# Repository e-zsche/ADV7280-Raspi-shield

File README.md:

# ADV7280 based analog video digitizer shield for raspberry pi

Raspberry pi shiel built around the ADV7280 analog video decoder IC. Connection to raspberry pi over
MIPI CSI-2 interface. FFC/FPC connector on the shield has the same pinout as the pi camera connector.

One huge advantage the ADV7280 has over similiar analog video decoders is that the drivers are already
present in the standard raspberry pi linux kernel. All you have to do is enable the driver in the
config.txt file. This shield is more or less plug'n'play.

# Hardware

The whole circuit design is copied exactly from the <a href="https://www.analog.com/media/en/technical-documentation/data-sheets/ADV7280.PDF">ADV7280 datasheet</a>

Video inputs are done with BNC connectors. The only reason is that I got these really cheap so I use
them everywhere. All video inputs are terminated with 75R resistors close to the connector. For
protection there are BAT54S diodes installed on all used inputs. Because of space constraints only
inputs 1 - 4 are available on the PCB.

In the beginning I was unsure how to set the RST, PWRDWN pins of the ADV7280 and how important
the power cycling is when booting the IC. That is what the jumper pins near the raspberry pi's
USB connectors are for. Turns out you can leave them all connected to +3.3V all the time.

I was unsure about the CAM_IO1 and CAM_IO2 pins of the raspberry CSI connector as well. The pins
on the pin header can be left unconnected.

The only really critical traces in my opinion are from the CSI output from the IC to the FFC/FPC
camera connector. Looking at the technical specs in the MIPI CSI standard these traces the traces
should have 100R differential impedance (+/- 10%). To get the correct trace width and spacing I
used kicad's builtin calculation tool and the PCB dimensions of the manufacturer. With these I
fiddled around with the calculation until it was close enough.

This design is routed for ordering at JLCPCB (not sponsored!). This is important because different
manufacturers may have different PCB dimensions, which in turn affects the trace impedance of the
CSI traces. Make sure to get this correct, otherwise the CSI connection may not work reliably.

Until now the shield is running fine and I encountered no problems while running.

# Software

All connections this shield needs for running is the CSI connector to the raspberry pi's camera
interface. Enabling the kernel module for this shield is done in the config.txt file:

```
[all]
# enable adv7280
dtoverlay=adv728x-m,adv7280m=1
```

Done! After booting you should get a ne video device.
You can check this with v4l2-ctl command line utility.

```
$ v4l2-ctl --list-devices
$ v4l2-ctl -D -d 0
```

## setting video standard

Video standard is set to NTSC as default. Change it with this command
```
$ v4l2-ctl --set-standard pal
$ v4l2-ctl --set-standard ntsc
```

## changing inputs

Selecting video input source is not straight forward. This is not streamlined in the driver.
Doing this is a little bit hacky, but it works.

```
$ sudo bash -c "echo 0 > /sys/module/adv7180/parameters/dbg_input"
```

Change the number to the input you want to select. 0 corresponds to input 1 and so forth.
You can check the detected input format with

```
$ v4l2-ctl -S
```

## picture adjustment

Here is the interesting part. You can adjust brightness, saturation and so on inside the ADV7280.
No need to fiddle around with i2c registers. When the driver is loaded the corresponding i2c bus
is not exposed for reading or writing. Instead everything is handled through the v4l2-ctl utility.

To list the available settings use one of these commands:

```
$ v4l2-ctl -d <device> -l
$ v4l2-ctl -d <device> -L
```

This gives a description of all available settings and also shows the value range for each setting. If you want to change something use this command:

```
$ v4l2-ctl -d <device> -c <setting>=<value>
```

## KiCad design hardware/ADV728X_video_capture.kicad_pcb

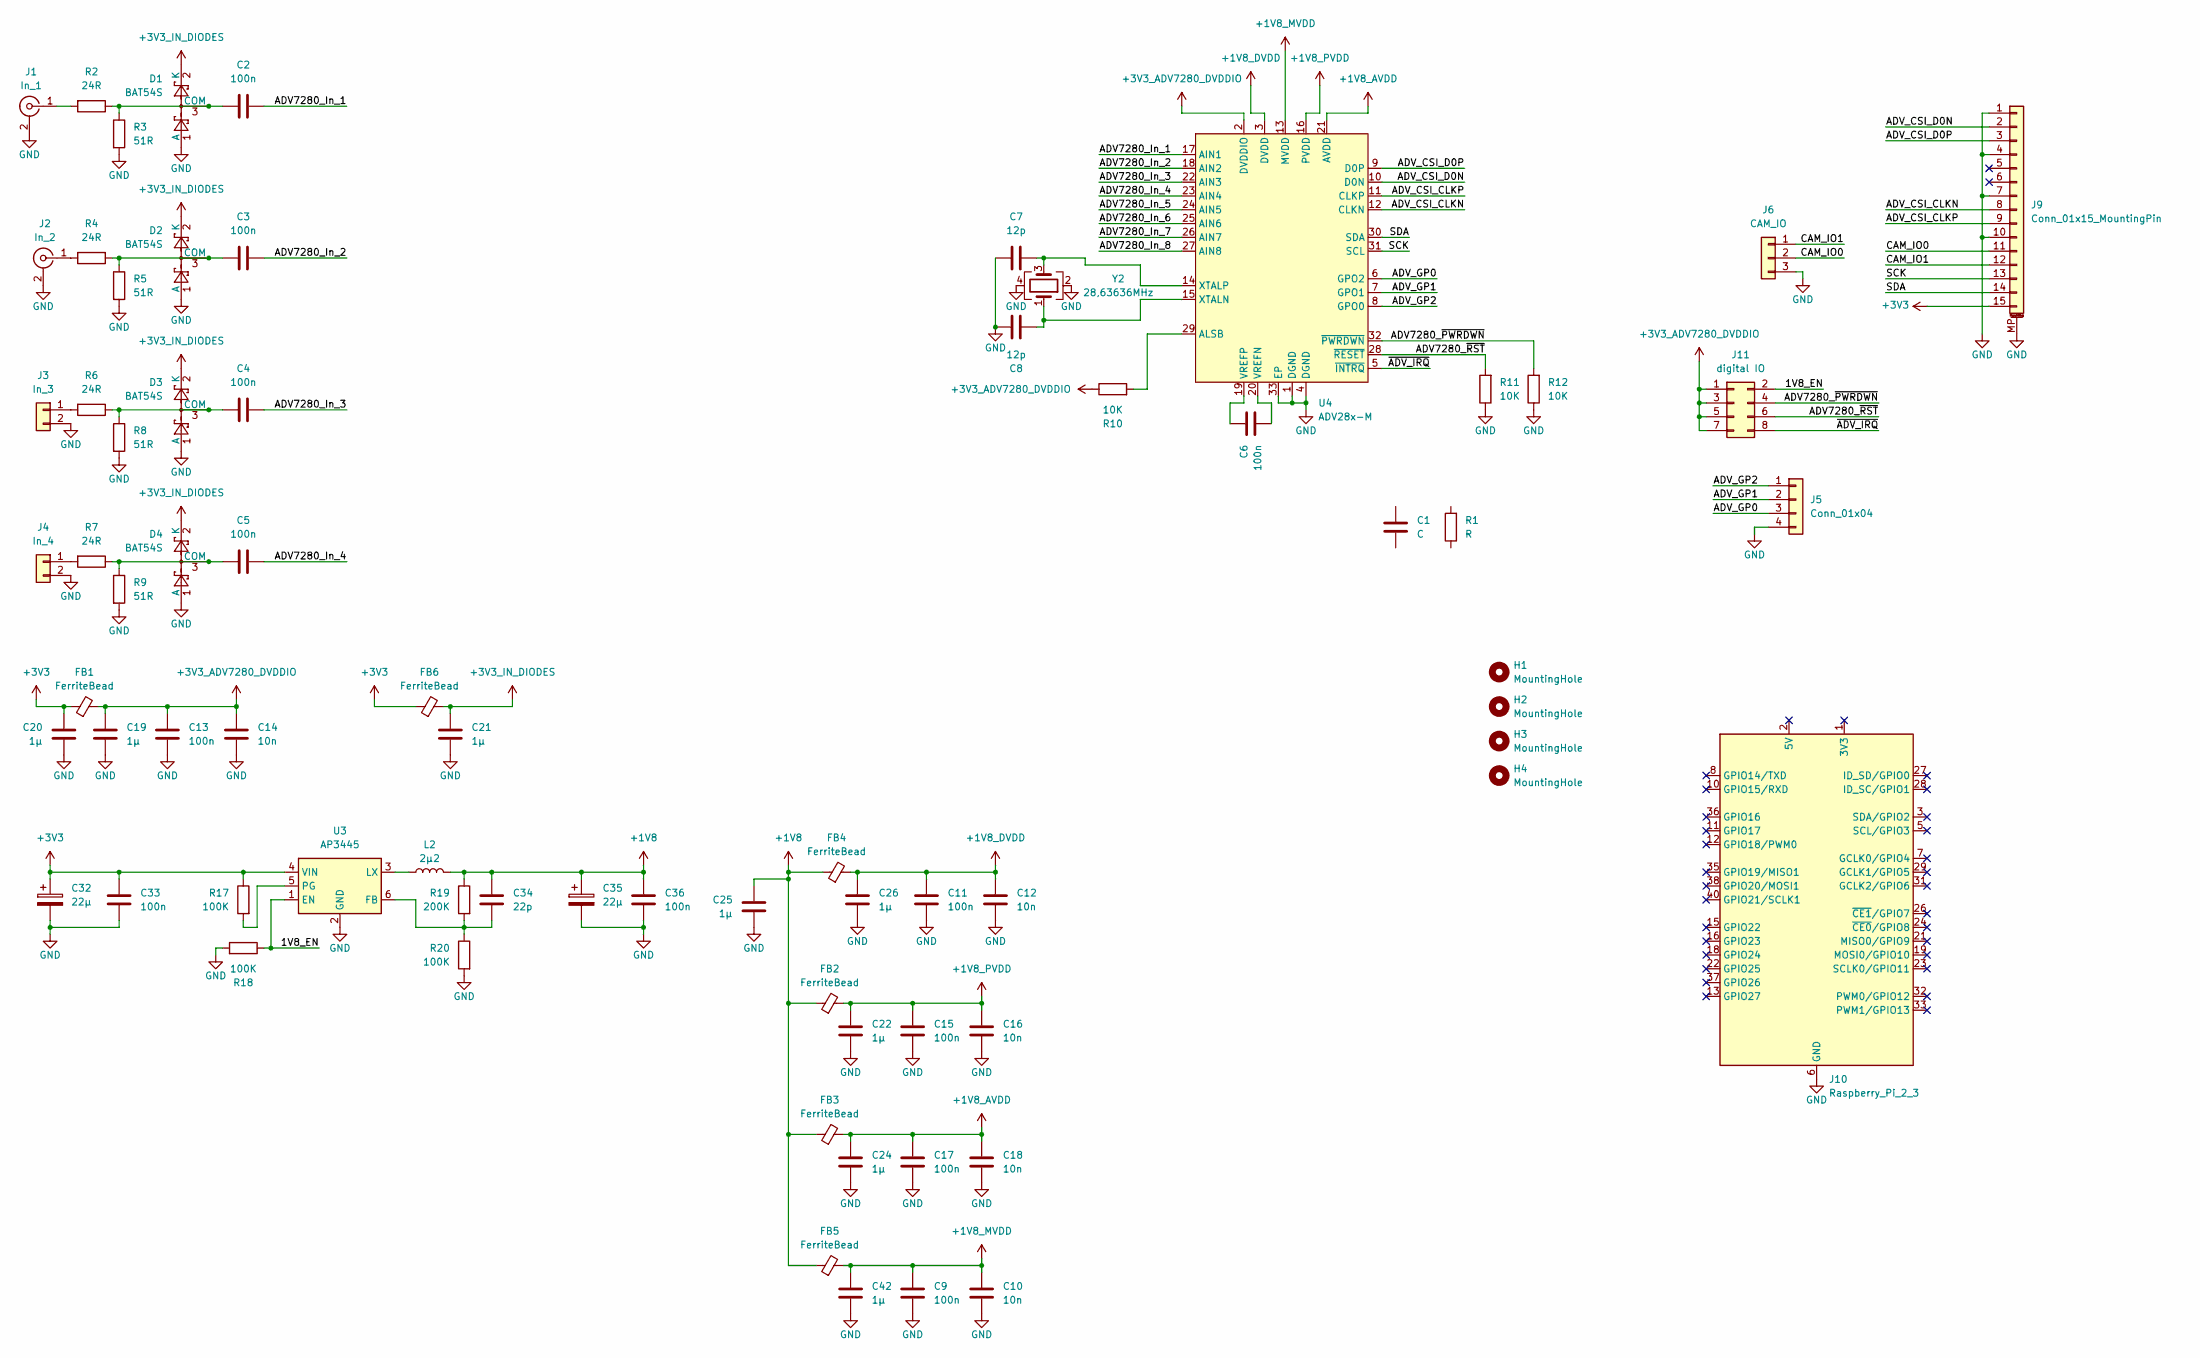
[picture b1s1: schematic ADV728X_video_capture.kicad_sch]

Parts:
C1: C
C2, C3, C4, C5, C6, C9, C11, C13, C15, C17, C33, C36: 100n; C_0402_1005Metric
C7, C8: 12p; C_0402_1005Metric
C10, C12, C14, C16, C18: 10n; C_0402_1005Metric
C19, C20, C21, C22, C24, C25, C26, C42: 1µ; C_0805_2012Metric
C32, C35: 22µ; C_0805_2012Metric
C34: 22p; C_0402_1005Metric
D1, D2, D3, D4: BAT54S; SOT-23
FB1, FB2, FB3, FB4, FB5, FB6: FerriteBead; L_0805_2012Metric
H1, H2, H3, H4: MountingHole; MountingHole_2.7mm_Pad
J1: In_1; BNC_Amphenol_B6252HB-NPP3G-50_Horizontal
J2: In_2; BNC_Amphenol_B6252HB-NPP3G-50_Horizontal
J3: In_3; PinHeader_1x02_P2.54mm_Vertical
J4: In_4; PinHeader_1x02_P2.54mm_Vertical
J5: Conn_01x04; PinHeader_1x04_P2.54mm_Vertical
J6: CAM_IO; PinHeader_1x03_P2.54mm_Vertical
J9: Conn_01x15_MountingPin; TE_1-84953-5_1x15-1MP_P1.0mm_Horizontal
J10: Raspberry_Pi_2_3; PinHeader_2x20_P2.54mm_Vertical
J11: digital IO; PinHeader_2x04_P2.54mm_Vertical
L2: 2µ2; L_1206_3216Metric_Pad1.22x1.90mm_HandSolder
R1: R
R2, R4, R6, R7: 24R; R_0805_2012Metric
R3, R5, R8, R9: 51R; R_0805_2012Metric
R10, R11, R12: 10K; R_0805_2012Metric
R17, R18, R20: 100K; R_0402_1005Metric_Pad0.72x0.64mm_HandSolder
R19: 200K; R_0402_1005Metric_Pad0.72x0.64mm_HandSolder
U3: AP3445; TSOT-23-6
U4: ADV28x-M; LFCSP-32-1EP_5x5mm_P0.5mm_EP3.6x3.6mm
Y2: 28,63636MHz; Crystal_SMD_3225-4Pin_3.2x2.5mm

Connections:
+1V8: C25.1, C34.1, C35.1, C36.1, FB2.1, FB3.1, FB4.1, FB5.1, L2.2, R19.1
+1V8_AVDD: C17.1, C18.1, C24.1, FB3.2, U4.21 (AVDD)
+1V8_DVDD: C11.1, C12.1, C26.1, FB4.2, U4.3 (DVDD)
+1V8_MVDD: C9.1, C10.1, C42.1, FB5.2, U4.13 (MVDD)
+1V8_PVDD: C15.1, C16.1, C22.1, FB2.2, U4.16 (PVDD)
+3V3: C20.1, C32.1, C33.1, FB1.1, FB6.1, J9.15, R17.1, U3.4 (VIN)
+3V3_ADV7280_DVDDIO: C13.1, C14.1, C19.1, FB1.2, J11.1, J11.3, J11.5, J11.7, R10.1, U4.2 (DVDDIO)
+3V3_IN_DIODES: C21.1, D1.2 (K), D2.2 (K), D3.2 (K), D4.2 (K), FB6.2
/1V8_EN: J11.2, R18.1, U3.1 (EN)
/ADV7280_In_1: C2.2, U4.17 (AIN1)
/ADV7280_In_2: C3.2, U4.18 (AIN2)
/ADV7280_In_3: C4.2, U4.22 (AIN3)
/ADV7280_In_4: C5.2, U4.23 (AIN4)
/ADV7280_In_5: U4.24 (AIN5)
/ADV7280_In_6: U4.25 (AIN6)
/ADV7280_In_7: U4.26 (AIN7)
/ADV7280_In_8: U4.27 (AIN8)
/ADV7280_~PWRDWN: J11.4, R12.2, U4.32 (~PWRDWN)
/ADV7280_~RST: J11.6, R11.2, U4.28 (~RESET)
/ADV_CSI_CLKN: J9.8, U4.12 (CLKN)
/ADV_CSI_CLKP: J9.9, U4.11 (CLKP)
/ADV_CSI_D0N: J9.2, U4.10 (D0N)
/ADV_CSI_D0P: J9.3, U4.9 (D0P)
/ADV_GP0: J5.3, U4.6 (GPO2)
/ADV_GP1: J5.2, U4.7 (GPO1)
/ADV_GP2: J5.1, U4.8 (GPO0)
/CAM_IO0: J6.2, J9.11
/CAM_IO1: J6.1, J9.12
/SCK: J9.13, U4.31 (SCL)
/SDA: J9.14, U4.30 (SDA)
/~ADV_IRQ: J11.8, U4.5 (~INTRQ)
GND: C7.1, C8.1, C9.2, C10.2, C11.2, C12.2, C13.2, C14.2, C15.2, C16.2, C17.2, C18.2, C19.2, C20.2, C21.2, C22.2, C24.2, C25.2, C26.2, C32.2, C33.2, C35.2, C36.2, C42.2, D1.1 (A), D2.1 (A), D3.1 (A), D4.1 (A), J1.2 (Ext), J2.2 (Ext), J3.2, J4.2, J5.4, J6.3, J9.1, J9.4, J9.7, J9.10, J9.MP (MountPin), J10.6 (GND), J10.9 (GND), J10.14 (GND), J10.20 (GND), J10.25 (GND), J10.30 (GND), J10.34 (GND), J10.39 (GND), R3.2, R5.2, R8.2, R9.2, R11.1, R12.1, R18.2, R20.2, U3.2 (GND), U4.1 (DGND), U4.4 (DGND), U4.33 (EP), Y2.2, Y2.4
unnamed: C2.1, D1.3 (COM), R2.1, R3.1
unnamed: C3.1, D2.3 (COM), R4.1, R5.1
unnamed: C4.1, D3.3 (COM), R6.1, R8.1
unnamed: C5.1, D4.3 (COM), R7.1, R9.1
unnamed: J1.1 (In), R2.2
unnamed: J2.1 (In), R4.2
unnamed: J3.1, R6.2
unnamed: J4.1, R7.2
unnamed: C34.2, R19.2, R20.1, U3.6 (FB)
unnamed: L2.1, U3.3 (LX)
unnamed: R17.2, U3.5 (PG)
unnamed: R10.2, U4.29 (ALSB)
unnamed: C6.2, U4.20 (VREFN)
unnamed: C6.1, U4.19 (VREFP)
unnamed: C8.2, U4.15 (XTALN), Y2.1
unnamed: C7.2, U4.14 (XTALP), Y2.3

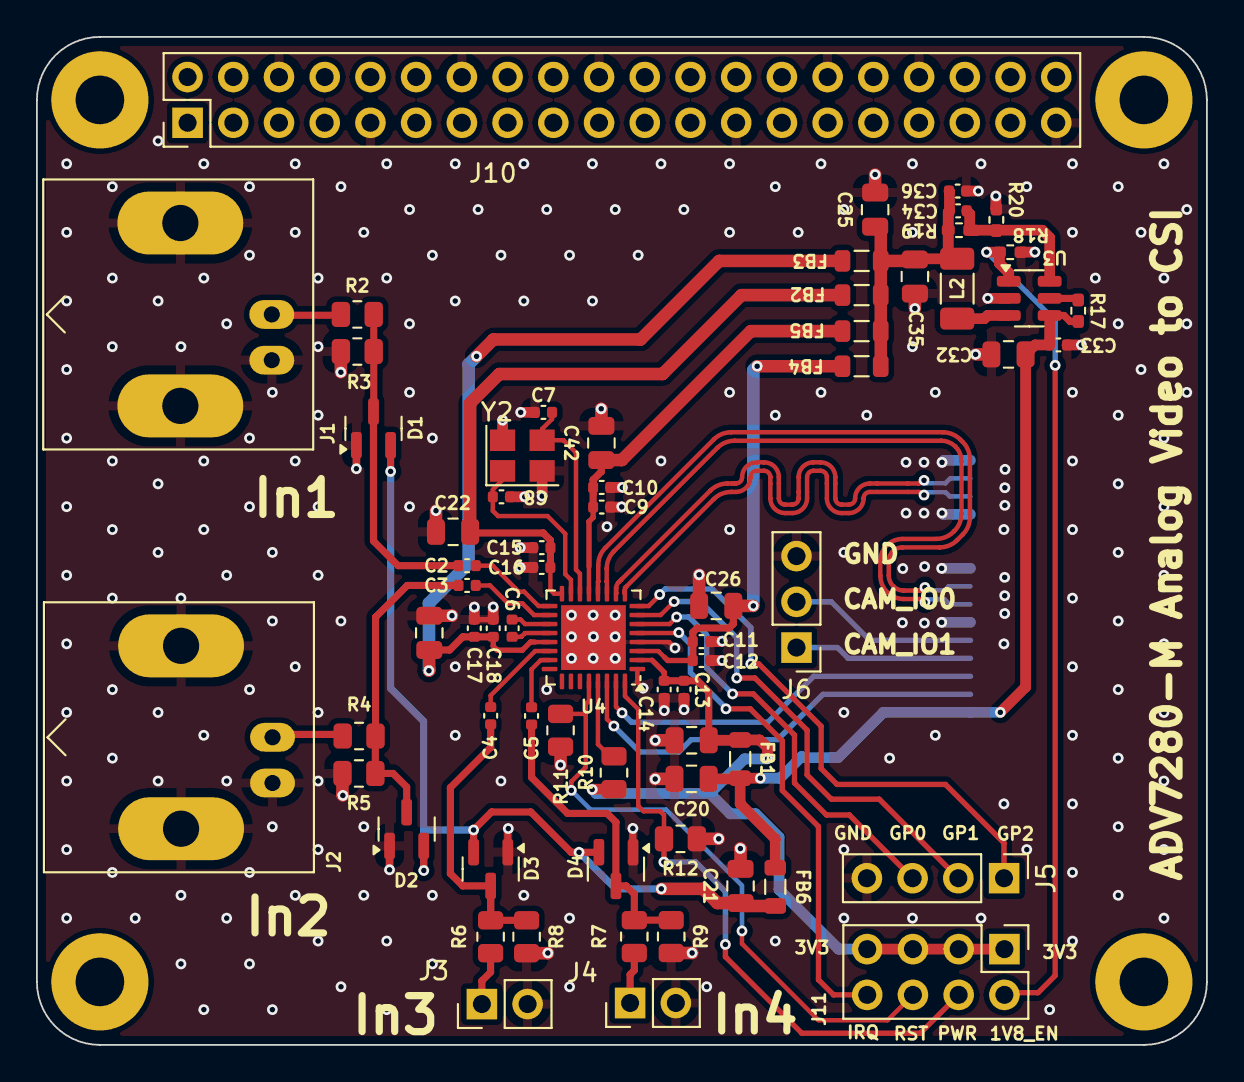
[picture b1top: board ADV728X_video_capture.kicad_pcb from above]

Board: 4 copper layers, 65.0 x 56.0 mm, 72 parts (1 on the bottom side), 44 nets.

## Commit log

2025-03-18 added README with project overview
2025-03-18 fixed img in README
2025-03-18 added raspi shield kicad project
2025-03-18 added harware section in README
2025-03-18 added software section in README
2025-03-18 config.txt example for using this shield
2025-03-18 added python library for controlling ADV7280
2025-03-18 added more info on controlling ADV7280 from software
2025-03-18 removed duplicate section
2025-03-18 added rendered PCB pics
2025-03-22 fixed links to ADV7280 documentation pdfs
